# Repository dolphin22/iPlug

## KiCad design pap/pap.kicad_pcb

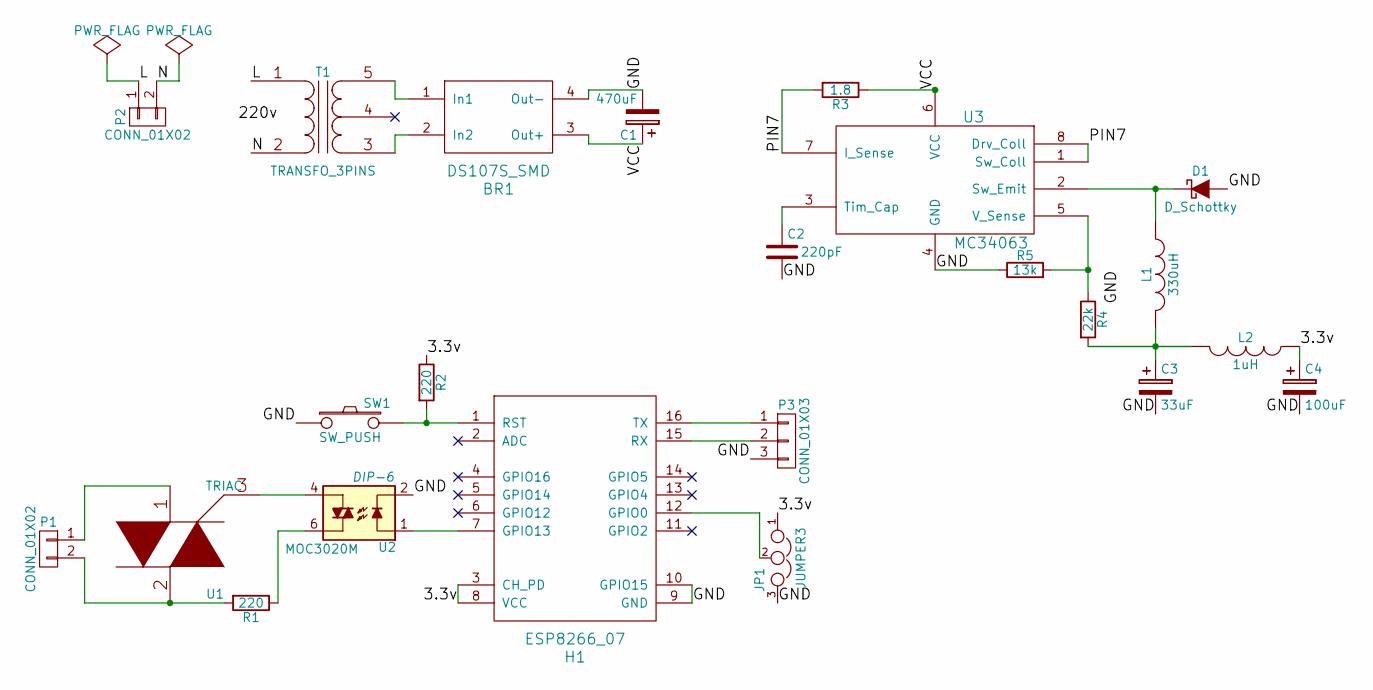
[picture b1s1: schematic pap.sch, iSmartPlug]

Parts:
BR1: DS107S_SMD
C1: 470uF; Elko_vert_11.5x8mm_RM3.5
C2: 220pF; C_Disc_D3_P2.5
C3: 33uF; Elko_vert_11x5mm_RM2
C4: 100uF; Elko_vert_11.5x8mm_RM3.5
D1: D_Schottky; Diode_DO-41_SOD81_Horizontal_RM10
H1: ESP8266_07
JP1: JUMPER3
L1: 330uH; Neosid_Air-Coil_SML_1turn_HDM0131A
L2: 1uH; Neosid_Air-Coil_SML_1turn_HDM0131A
P1, P2: CONN_01X02; Pin_Header_Angled_1x02
P3: CONN_01X03
R1, R2: 220; Resistor_Horizontal_RM10mm
R3: 1.8; Resistor_Horizontal_RM10mm
R4: 22k; Resistor_Horizontal_RM10mm
R5: 13k; Resistor_Horizontal_RM10mm
SW1: SW_PUSH
T1: TRANSFO_3PINS
U1: TRIAC
U2: MOC3020M; DIP-6
U3: MC34063

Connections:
/3.3v: C4.1, H1.3 (CH_PD), H1.8 (VCC), JP1.1, L2.1, R2.1
/GND: BR1.4 (Out-), C1.2, C2.2, C3.2, C4.2, D1.1 (A), H1.9 (GND), H1.10 (GPIO15), JP1.3, P3.3, R5.1, SW1.1, U2.2, U3.4 (GND)
/L: P2.1, T1.1 (AA)
/N: P2.2, T1.2 (AB)
/PIN7: R3.2, U3.1 (Sw_Coll), U3.7 (I_Sense), U3.8 (Drv_Coll)
/VCC: BR1.3 (Out+), C1.1, R3.1, U3.6 (VCC)
unnamed: BR1.1 (In1), T1.5 (SC)
unnamed: BR1.2 (In2), T1.3 (SA)
unnamed: C2.1, U3.3 (Tim_Cap)
unnamed: C3.1, L1.2, L2.2, R4.2
unnamed: D1.2 (K), L1.1, U3.2 (Sw_Emit)
unnamed: H1.1 (RST), R2.2, SW1.2
unnamed: H1.7 (GPIO13), U2.1
unnamed: H1.12 (GPIO0), JP1.2
unnamed: H1.15 (RX), P3.2
unnamed: H1.16 (TX), P3.1
unnamed: P1.1, U1.1
unnamed: P1.2, R1.2, U1.2
unnamed: R1.1, U2.6
unnamed: R4.1, R5.2, U3.5 (V_Sense)
unnamed: U1.3, U2.4

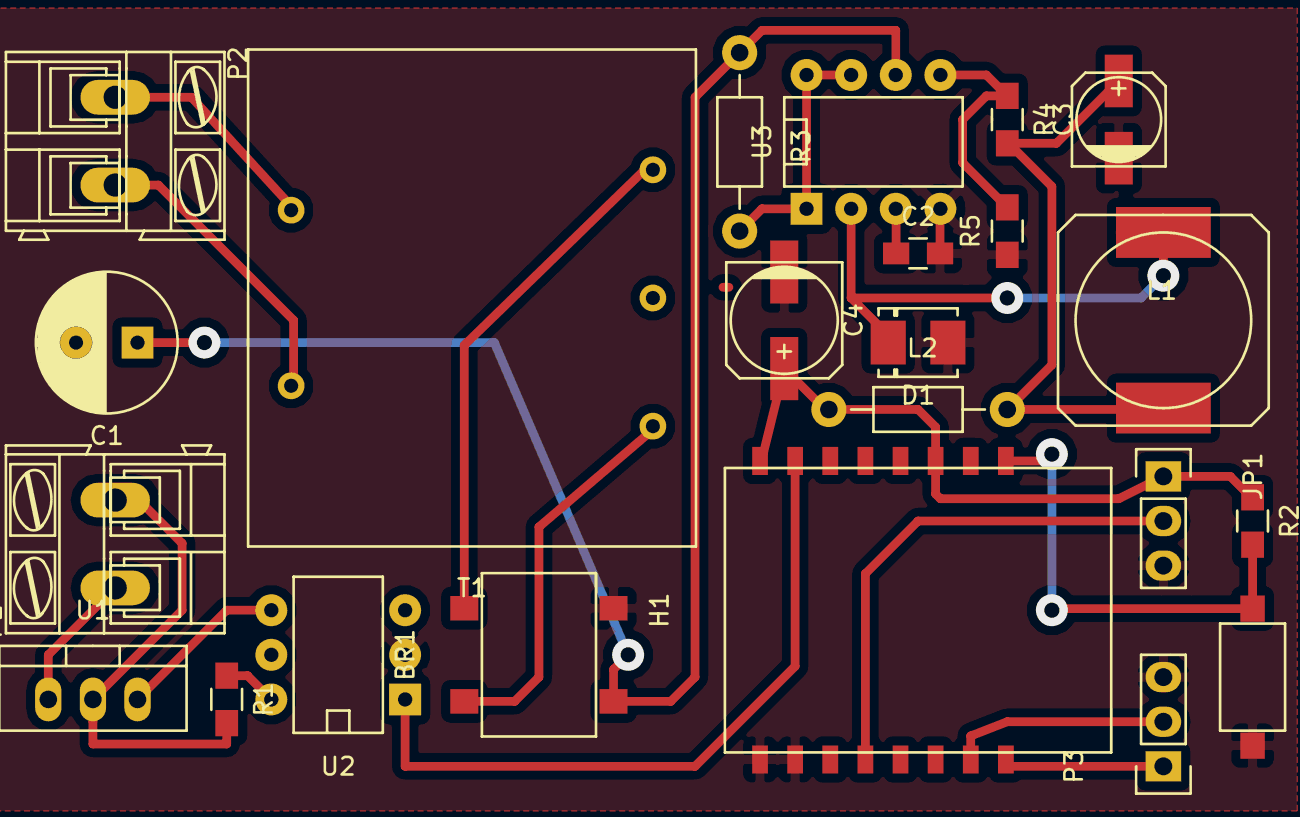
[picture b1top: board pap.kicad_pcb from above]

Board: 2 copper layers, 23 parts (0 on the bottom side), 21 nets.

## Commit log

2015-04-09 Added files.
2015-04-10 Misc. updates.
